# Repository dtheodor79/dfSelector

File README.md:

# Wireless DF selector
 The Wireless DF (WDF) selector allows users to boot an Amiga 500 from an internal or external drive. Instead of using a mechanical switch or multiple reset sequences to toggle between DF0 and DF1, WDF can be configured over a wireless connection. 
 
# Why bother?
Well, all this started because I don't like modifying my A500's precious case (like drilling to install a switch) 🙂. Also, I find more elegant using wireless commands to toggle between DF0 and DF1, than multiple resets 😎.
 
# Concept
The WDF concept is illustrated below: 

Pins 13 (sel0) and 14 (sel1) from 8520A (even CIA) are connected to an MCU with wireless connection capability. Users can configure from an external device how these signals are forwarded to the A500 motherboard (MB), in order to select from which floppy drive the computer shall boot. 

# Demo video

# Implementation
The images below show three WDF 3D models that are implemented with an ESP32 MCU, enabling switch configuration over Bluetooth connections:

ESP32 "in front" of 8520A (click [here](https://www.pcbway.com/project/shareproject/Amiga_500_Wireless_DF_selector.html) to build one):

ESP32 "behind" 8520A:

ESP32 "stacked" on top of 8520A (click [here](https://www.pcbway.com/project/shareproject/Amiga_500_compact_wireless_DF_selector.html) to build one):

A voltage convertor between 3.3V and 5V is used to allow communication between the ESP32 (3.3V) and the 8520A (5V). In addition, since the first WDF version (ESP32 "in front" of 8520A) is placed above the floppy ribbon cable connector of the A500, it requires long pin headers (such as the one below) to connect to the A500 MB:

# How to use the ESP32-based implementation
The current ESP32 firmware advertises a Bluetooth-enabled device with the name "A500 DF Selector". You will need another Bluetooth-enabled device to connect to the WDF and then send raw data for configuring the sel0 and sel1 switching. An easy way is to download a simple Bluetooth app to your smartphone that allows sending raw data to other devices. 

## Toggle DF1 as bootable:

* Make sure that there is no disk in DF0.
* Power-up the A500 and wait for few secs (e.g. 5).
* Scan for the "A500 DF Selector" device, and when found, connect to it.
* Send "df1".
* Power-down the A500 for a few secs.
* Power-up again, and now the A500 should boot from DF1.

## Toggle DF0 as bootable:

* Make sure that there is no disk (or adf image that will boot) in DF1.
* Power-up the A500 and wait for few secs (e.g. 5).
* Scan for the "A500 DF Selector" device, and when found, connect to it.
* Send "df0".
* Power-down the A500 for a few secs.
* Power-up again, and now the A500 should boot from DF0.

# Important notes
- All tests were carried out with a modified PC-floppy as DF0 and a Gotek emulator as DF1 (but jumper set to S0). As you can see in the demo video above, floppy selection could be done seamlessly without even restarting the A500 💣, by sending "df0" and "df1" commands when there was no floppy access. If you would like to try it, please be careful and always make sure before sending any command that there is no floppy access (don't blame me if there is any damage though 😛). 
- When DF0 is selected, the current firmware  
  - forwards sel0 (8520A) ➡️ sel0 (A500 MB)
  - sets sel1 (A500 MB) ➡️ HIGH
- When DF1 is selected, the current firmware  
  - forwards sel0 (8520A) ➡️ sel1 (A500 MB)
  - forwards sel1 (8520A) ➡️ sel0 (A500 MB)

Feel free to change how the firmware handles switching, so it suits to your configuration 😉.

# Pictures of the ESP32 implementation
Here are a few images of the final prototype on my A500.

WDF mounted above the floppy ribbon cable connector:

Loading Cannon Fodder from the Gotek emulator as DF1:

Another view of the WDF mounted above the floppy ribbon cable connector:

Gotek emulator connected externally:

Hope you find it useful!! 😎

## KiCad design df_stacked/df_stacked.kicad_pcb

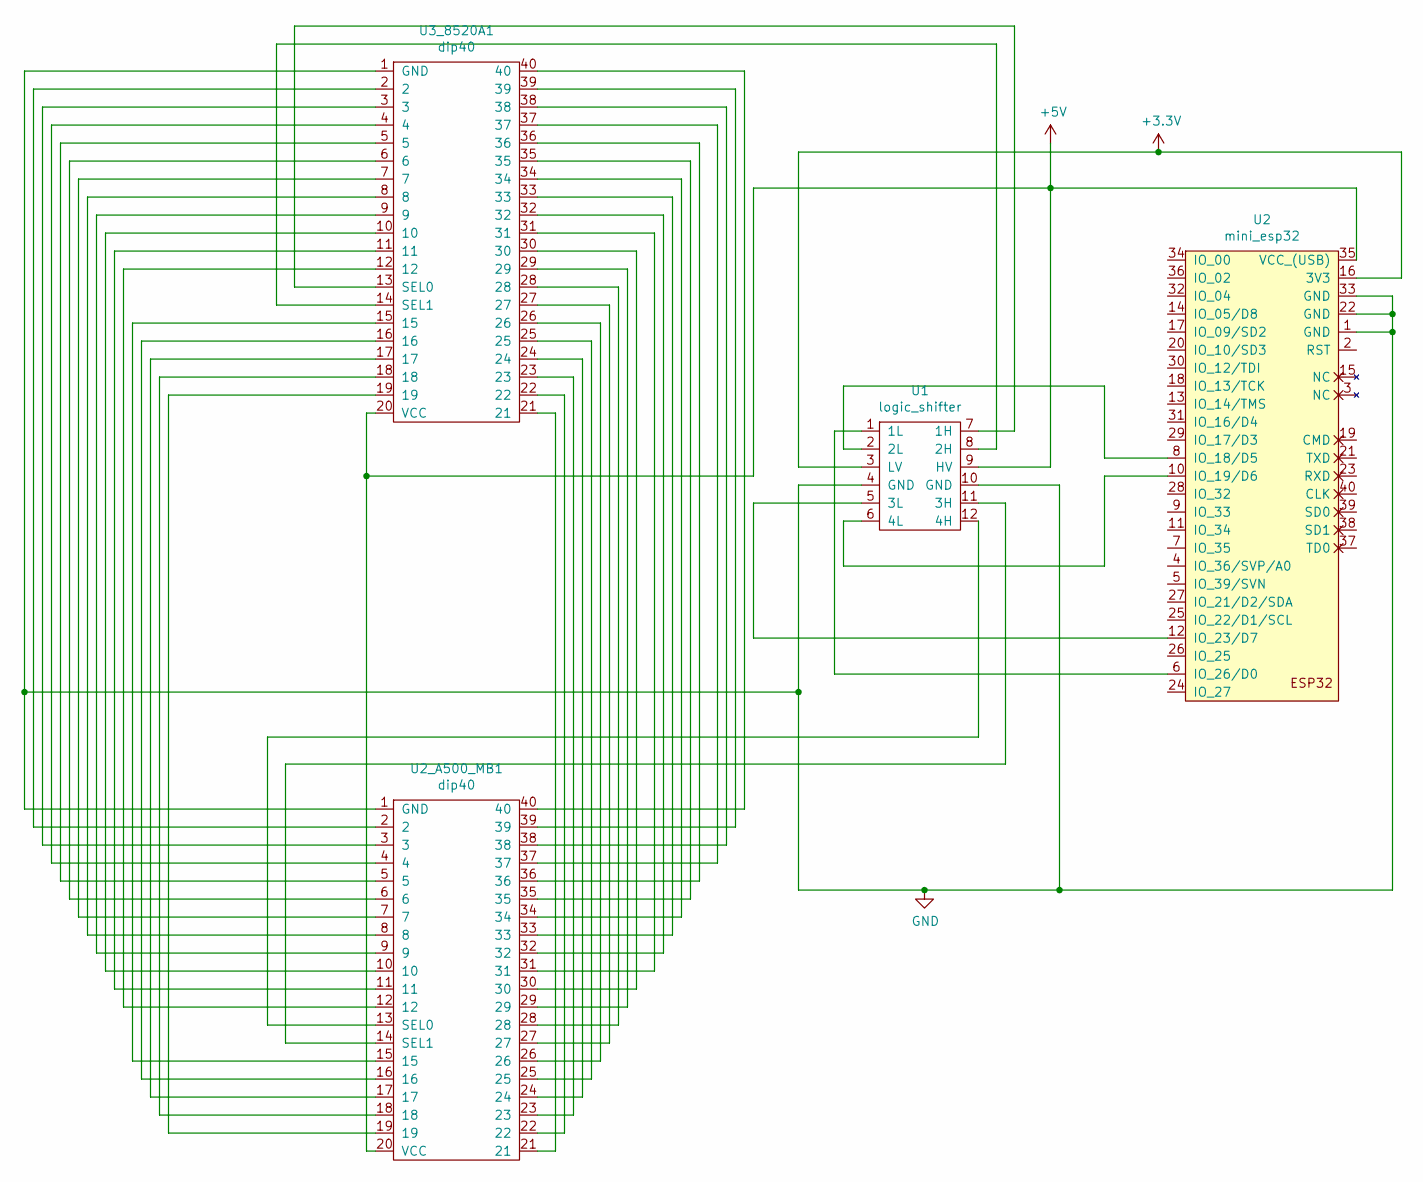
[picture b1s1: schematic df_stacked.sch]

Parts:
U1: logic_shifter; 4channel_logic_shifter
U2: mini_esp32; ESP32_mini
U2_A500_MB1, U3_8520A1: dip40; DIP-40_W15.24mm

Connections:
+3V3: U1.3 (LV), U2.16 (3V3)
+5V: U1.9 (HV), U2.35 (VCC_(USB)), U2_A500_MB1.20 (VCC), U3_8520A1.20 (VCC)
GND: U1.4 (GND), U1.10 (GND), U2.1 (GND), U2.22 (GND), U2.33 (GND), U2_A500_MB1.1 (GND), U3_8520A1.1 (GND)
unnamed: U1.1 (1L), U2.6 (IO_26/D0)
unnamed: U1.2 (2L), U2.8 (IO_18/D5)
unnamed: U1.5 (3L), U2.12 (IO_23/D7)
unnamed: U1.6 (4L), U2.10 (IO_19/D6)
unnamed: U1.7 (1H), U3_8520A1.13 (SEL0)
unnamed: U1.8 (2H), U3_8520A1.14 (SEL1)
unnamed: U1.11 (3H), U2_A500_MB1.14 (SEL1)
unnamed: U1.12 (4H), U2_A500_MB1.13 (SEL0)
unnamed: U2_A500_MB1.2, U3_8520A1.2
unnamed: U2_A500_MB1.3, U3_8520A1.3
unnamed: U2_A500_MB1.4, U3_8520A1.4
unnamed: U2_A500_MB1.5, U3_8520A1.5
unnamed: U2_A500_MB1.6, U3_8520A1.6
unnamed: U2_A500_MB1.7, U3_8520A1.7
unnamed: U2_A500_MB1.8, U3_8520A1.8
unnamed: U2_A500_MB1.9, U3_8520A1.9
unnamed: U2_A500_MB1.10, U3_8520A1.10
unnamed: U2_A500_MB1.11, U3_8520A1.11
unnamed: U2_A500_MB1.12, U3_8520A1.12
unnamed: U2_A500_MB1.15, U3_8520A1.15
unnamed: U2_A500_MB1.16, U3_8520A1.16
unnamed: U2_A500_MB1.17, U3_8520A1.17
unnamed: U2_A500_MB1.18, U3_8520A1.18
unnamed: U2_A500_MB1.19, U3_8520A1.19
unnamed: U2_A500_MB1.21, U3_8520A1.21
unnamed: U2_A500_MB1.22, U3_8520A1.22
unnamed: U2_A500_MB1.23, U3_8520A1.23
unnamed: U2_A500_MB1.24, U3_8520A1.24
unnamed: U2_A500_MB1.25, U3_8520A1.25
unnamed: U2_A500_MB1.26, U3_8520A1.26
unnamed: U2_A500_MB1.27, U3_8520A1.27
unnamed: U2_A500_MB1.28, U3_8520A1.28
unnamed: U2_A500_MB1.29, U3_8520A1.29
unnamed: U2_A500_MB1.30, U3_8520A1.30
unnamed: U2_A500_MB1.31, U3_8520A1.31
unnamed: U2_A500_MB1.32, U3_8520A1.32
unnamed: U2_A500_MB1.33, U3_8520A1.33
unnamed: U2_A500_MB1.34, U3_8520A1.34
unnamed: U2_A500_MB1.35, U3_8520A1.35
unnamed: U2_A500_MB1.36, U3_8520A1.36
unnamed: U2_A500_MB1.37, U3_8520A1.37
unnamed: U2_A500_MB1.38, U3_8520A1.38
unnamed: U2_A500_MB1.39, U3_8520A1.39
unnamed: U2_A500_MB1.40, U3_8520A1.40

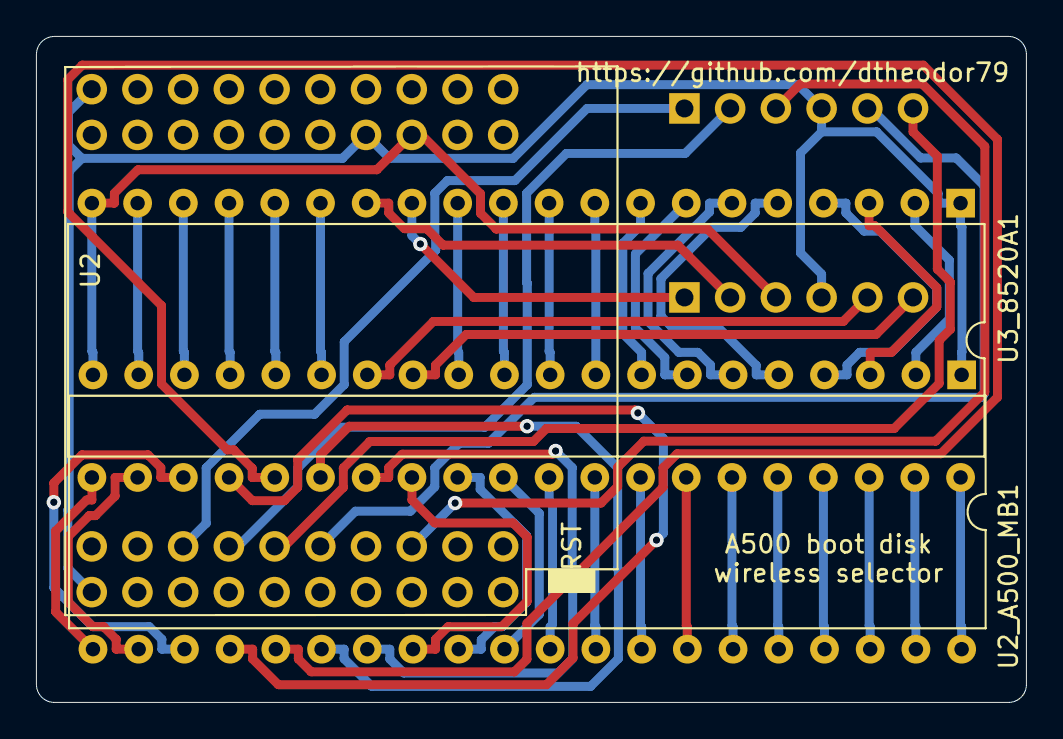
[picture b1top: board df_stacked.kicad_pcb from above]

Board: 2 copper layers, 55.0 x 37.0 mm, 4 parts (1 on the bottom side), 47 nets.

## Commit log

2021-12-01 added images
2021-12-01 images
2021-12-01 updated ble client test
2021-12-02 added inverted df selector
2021-12-03 added stacked pcb
2021-12-03 added bom
2021-12-03 gerbers
2022-01-14 Update fp-info-cache
